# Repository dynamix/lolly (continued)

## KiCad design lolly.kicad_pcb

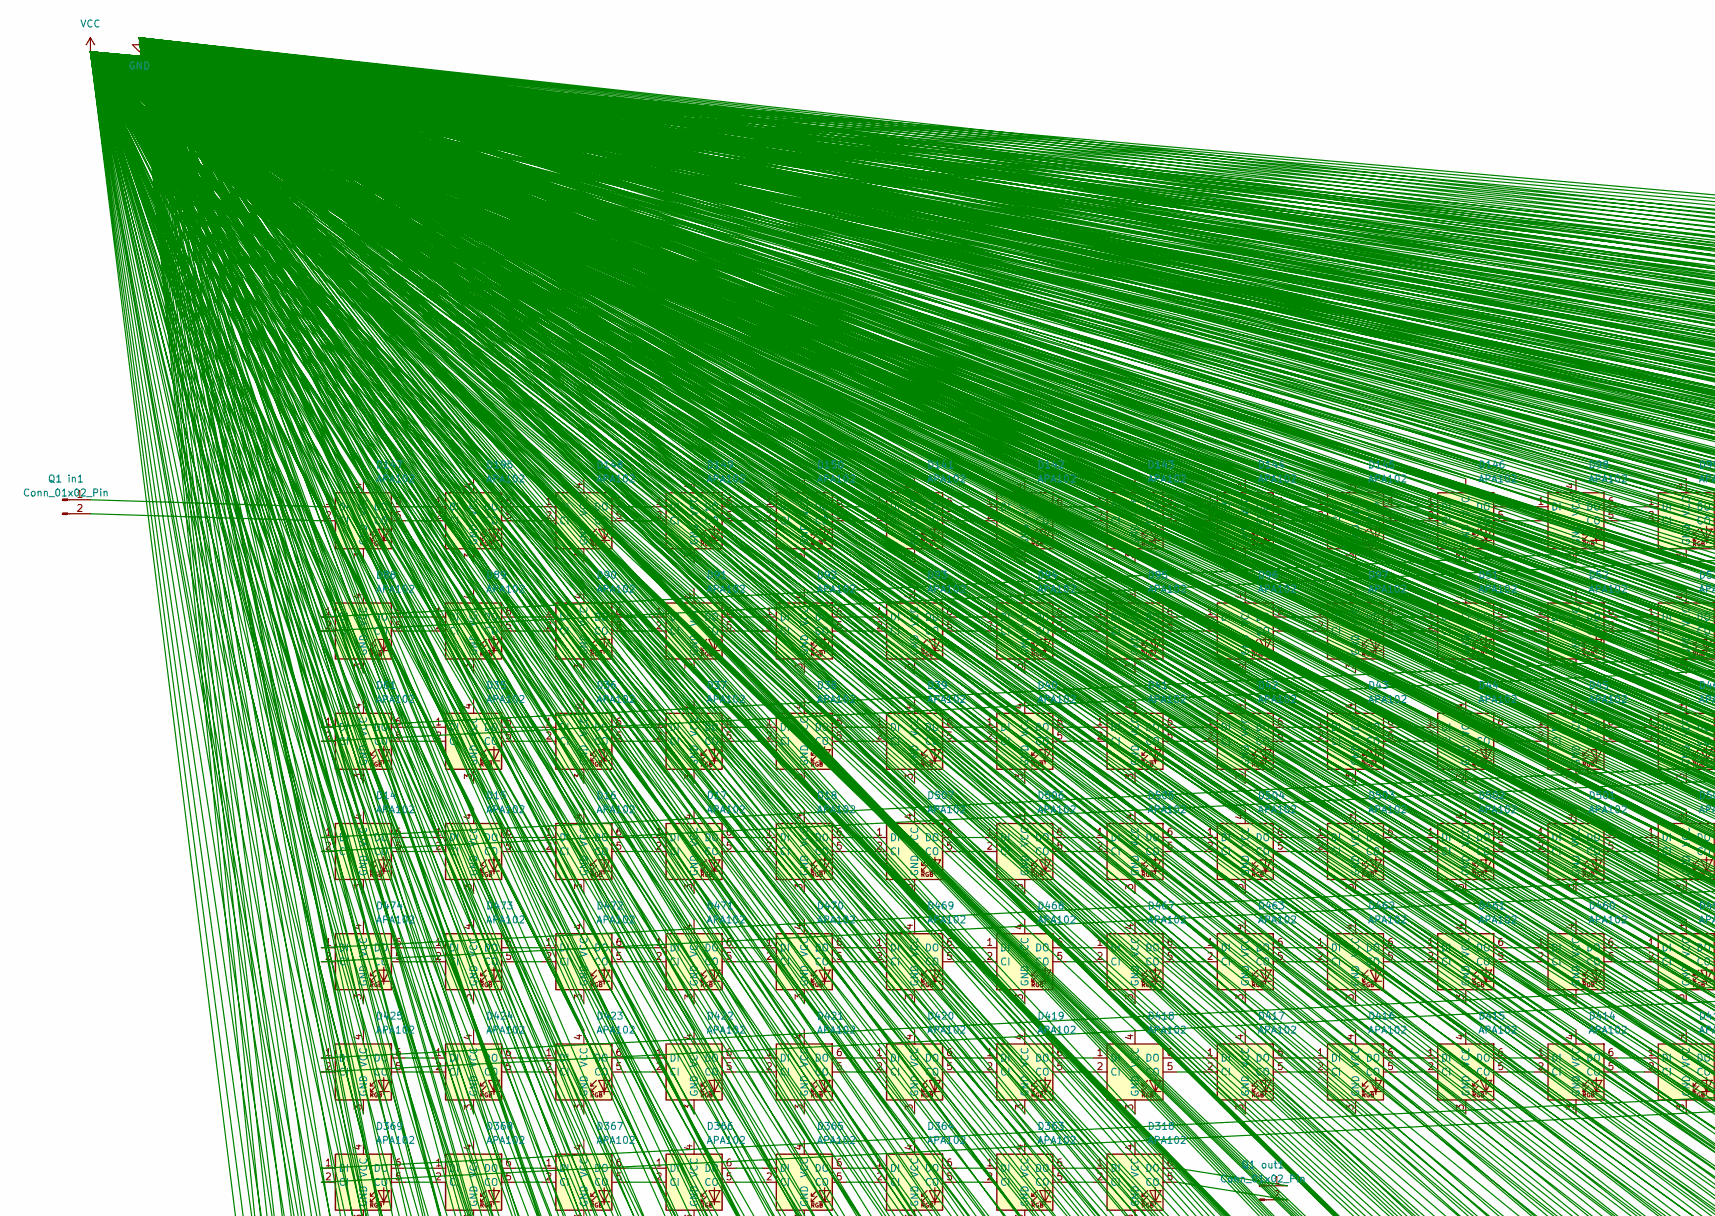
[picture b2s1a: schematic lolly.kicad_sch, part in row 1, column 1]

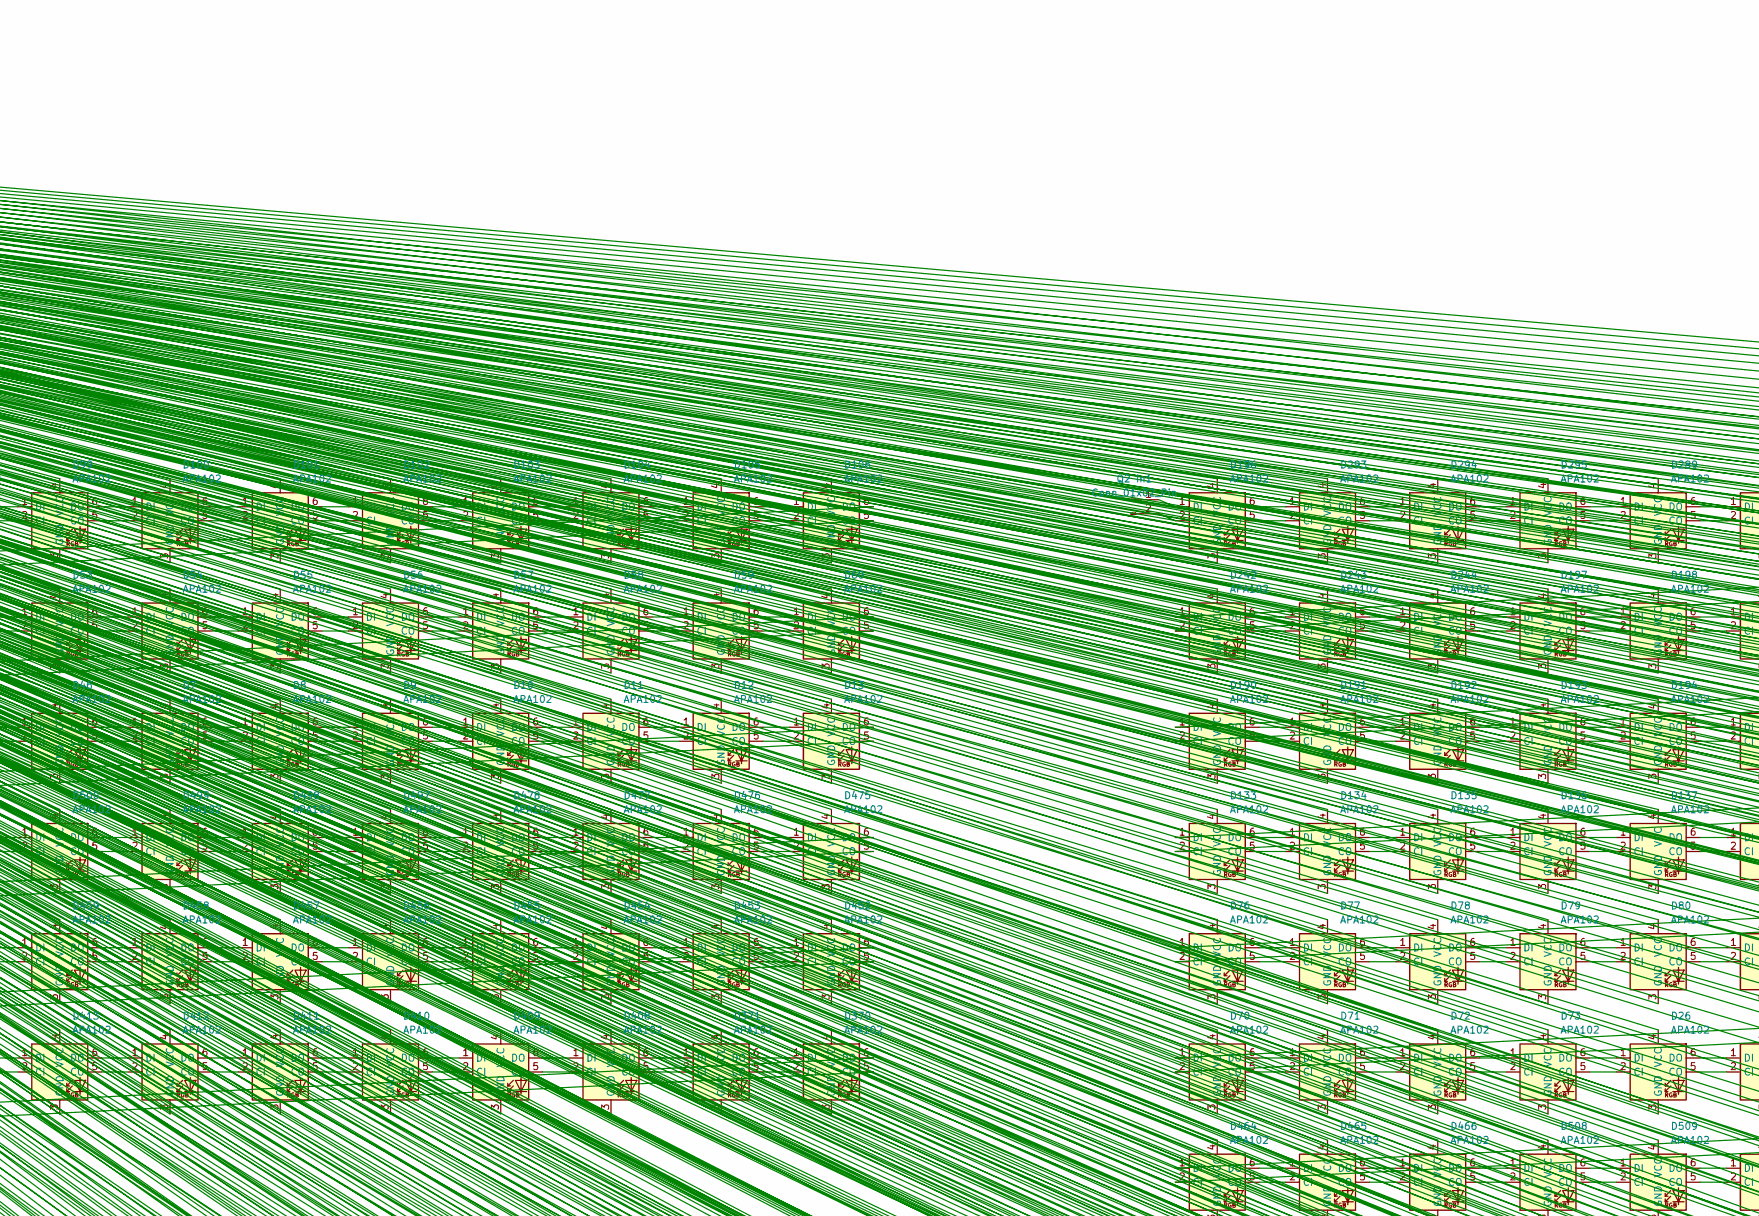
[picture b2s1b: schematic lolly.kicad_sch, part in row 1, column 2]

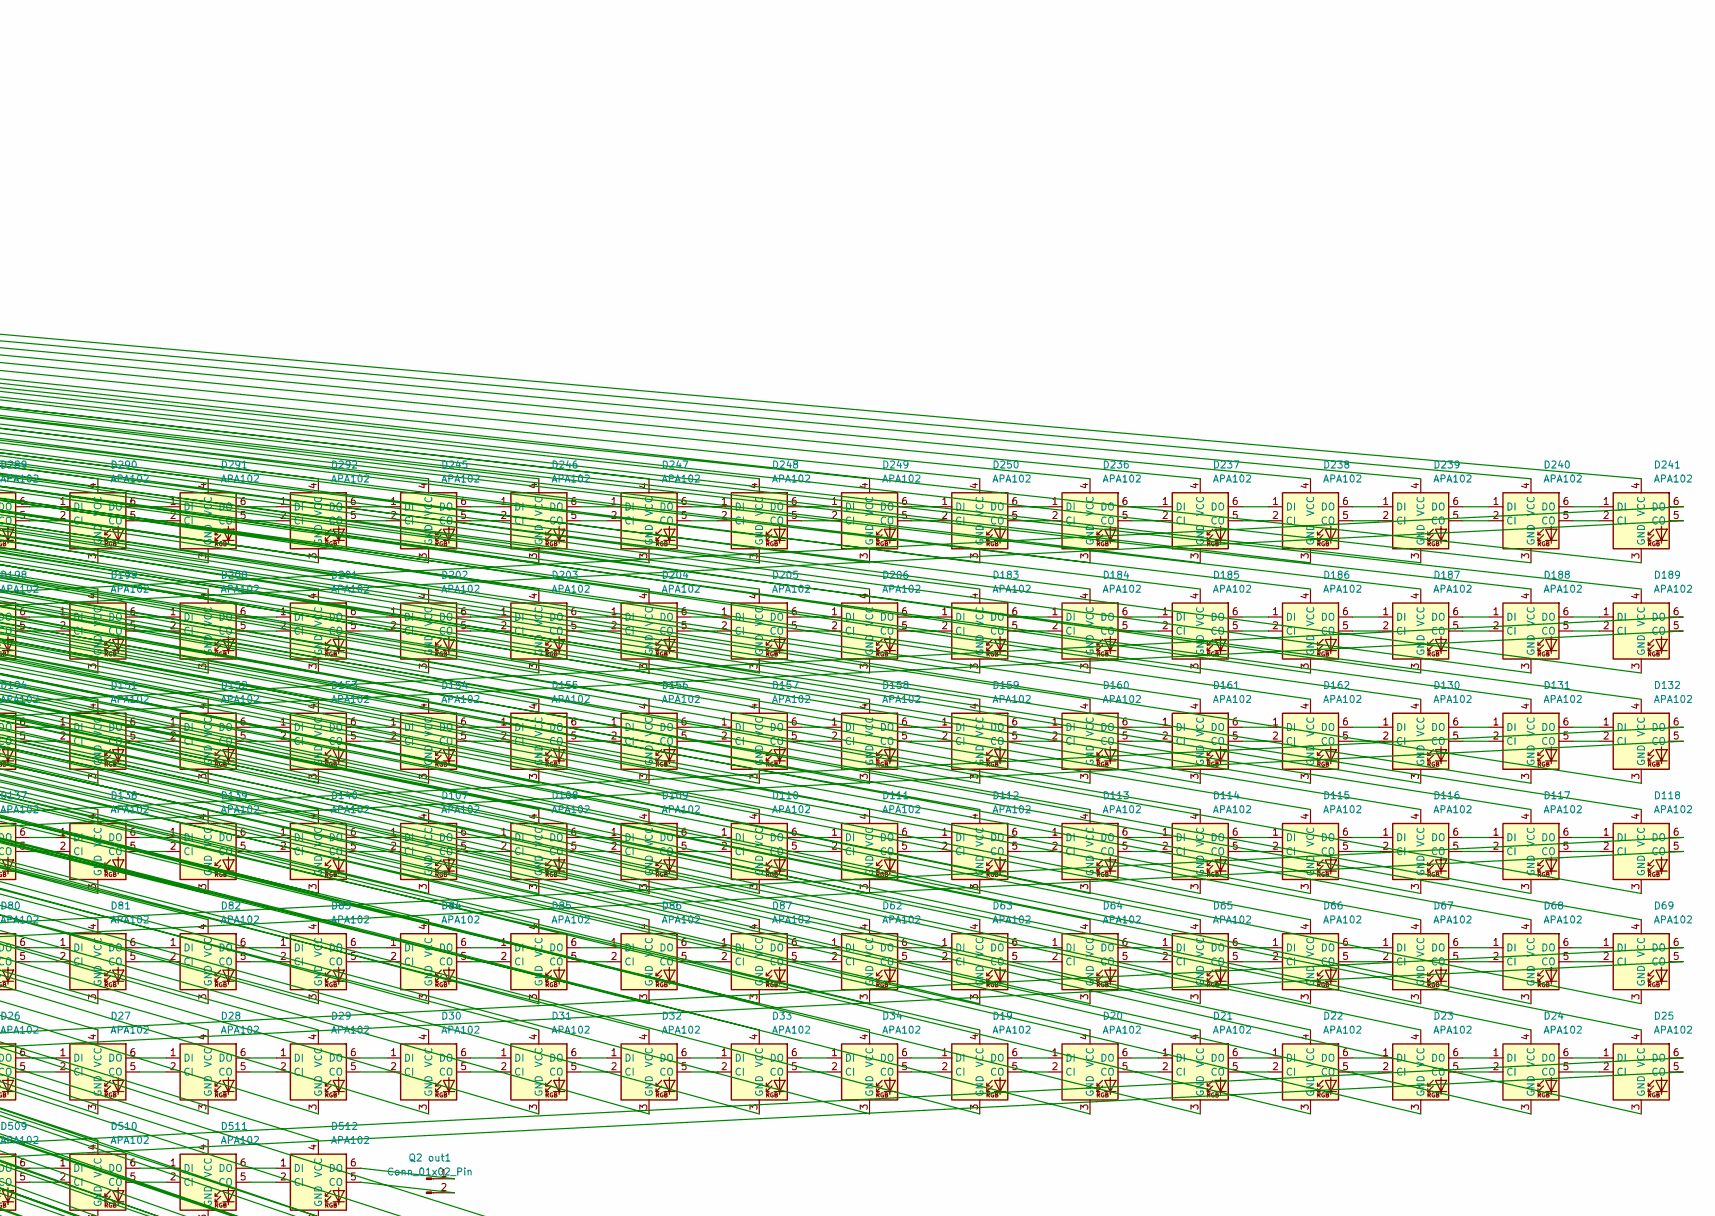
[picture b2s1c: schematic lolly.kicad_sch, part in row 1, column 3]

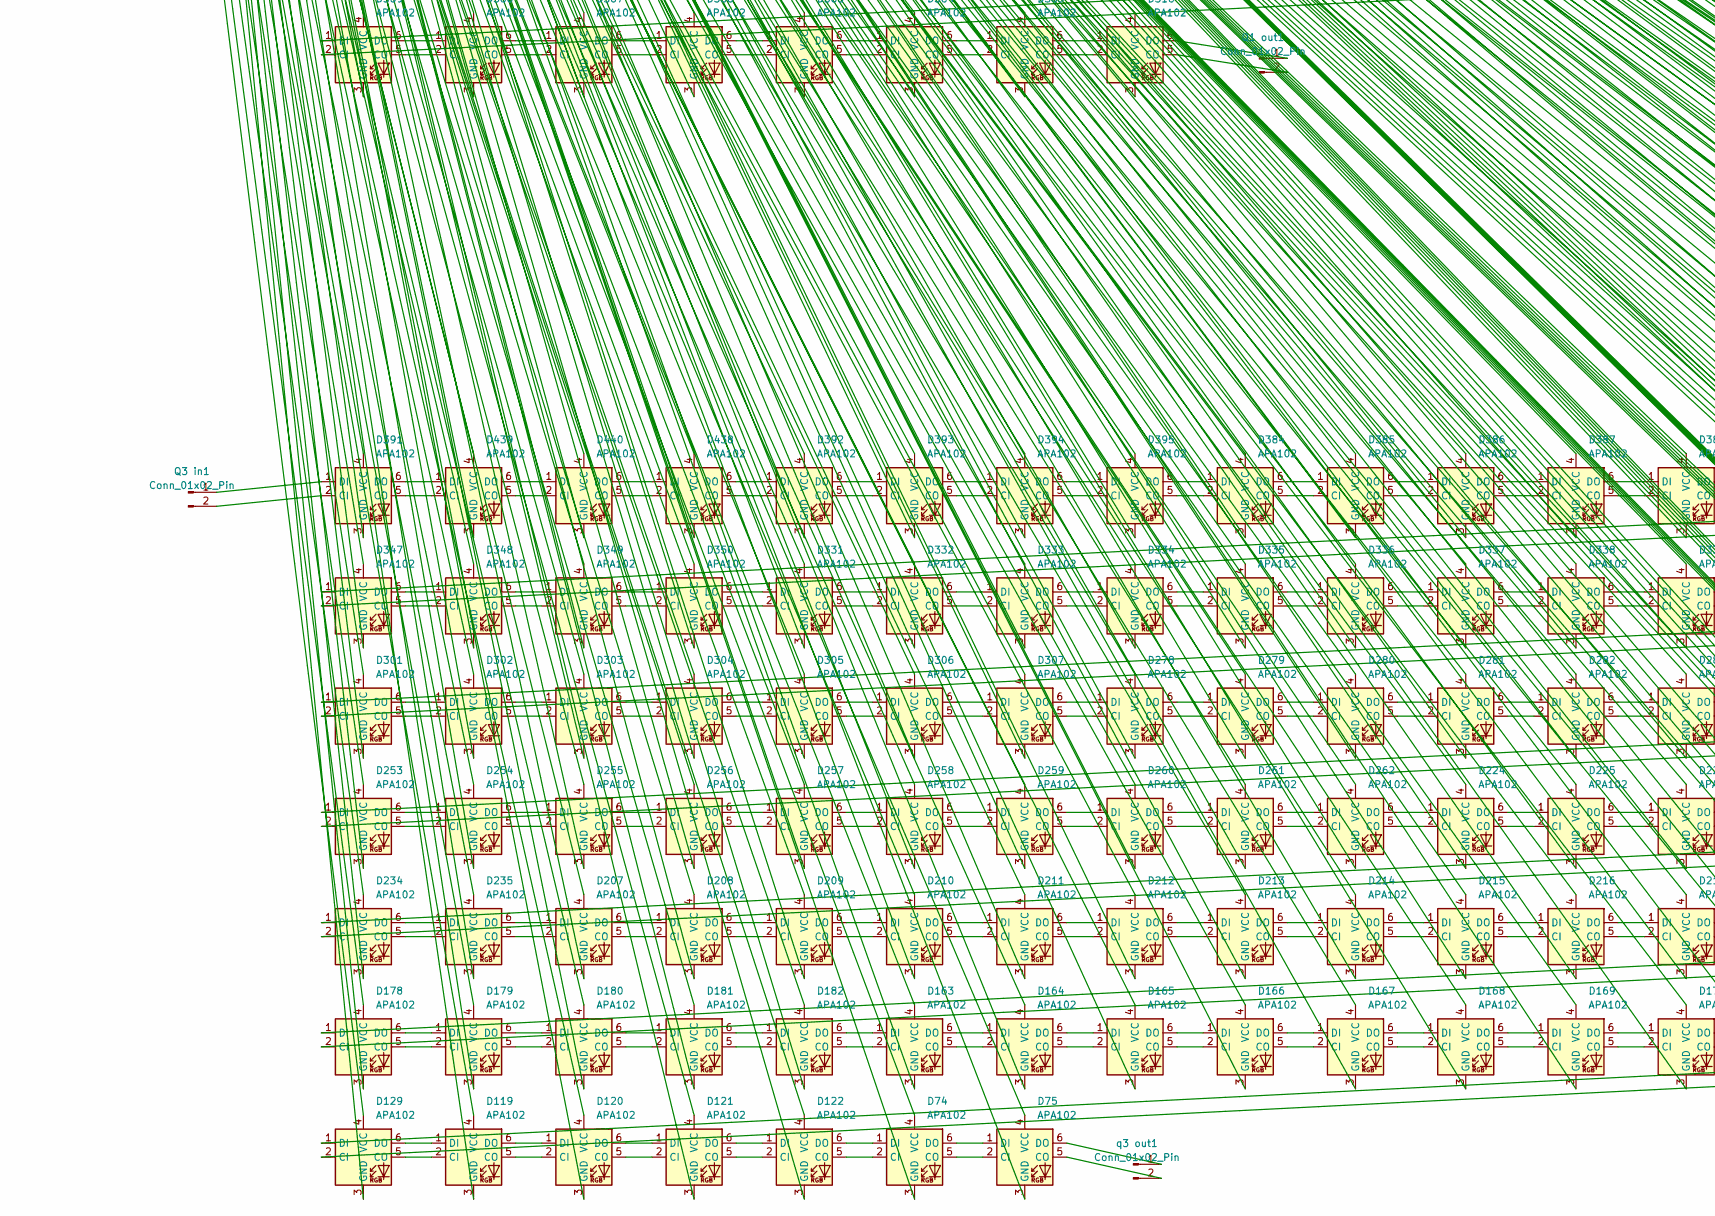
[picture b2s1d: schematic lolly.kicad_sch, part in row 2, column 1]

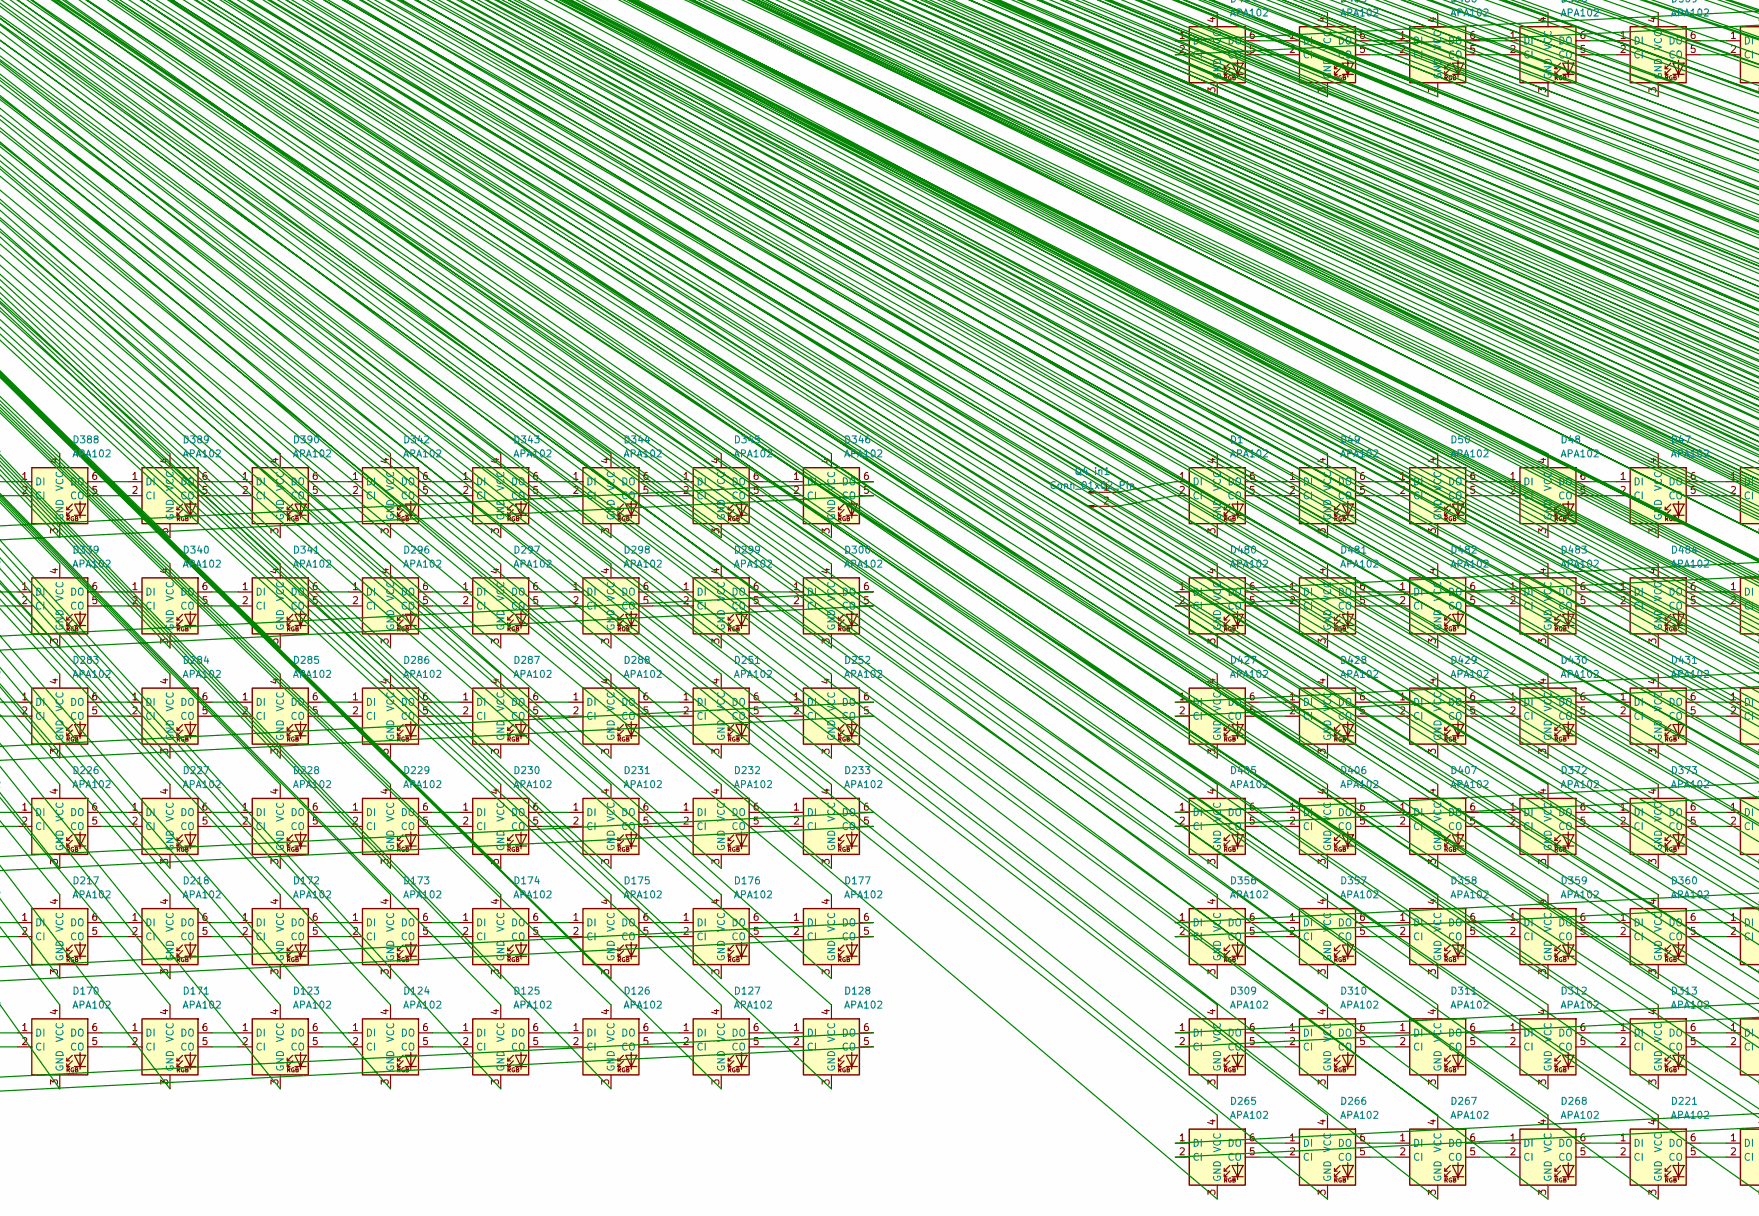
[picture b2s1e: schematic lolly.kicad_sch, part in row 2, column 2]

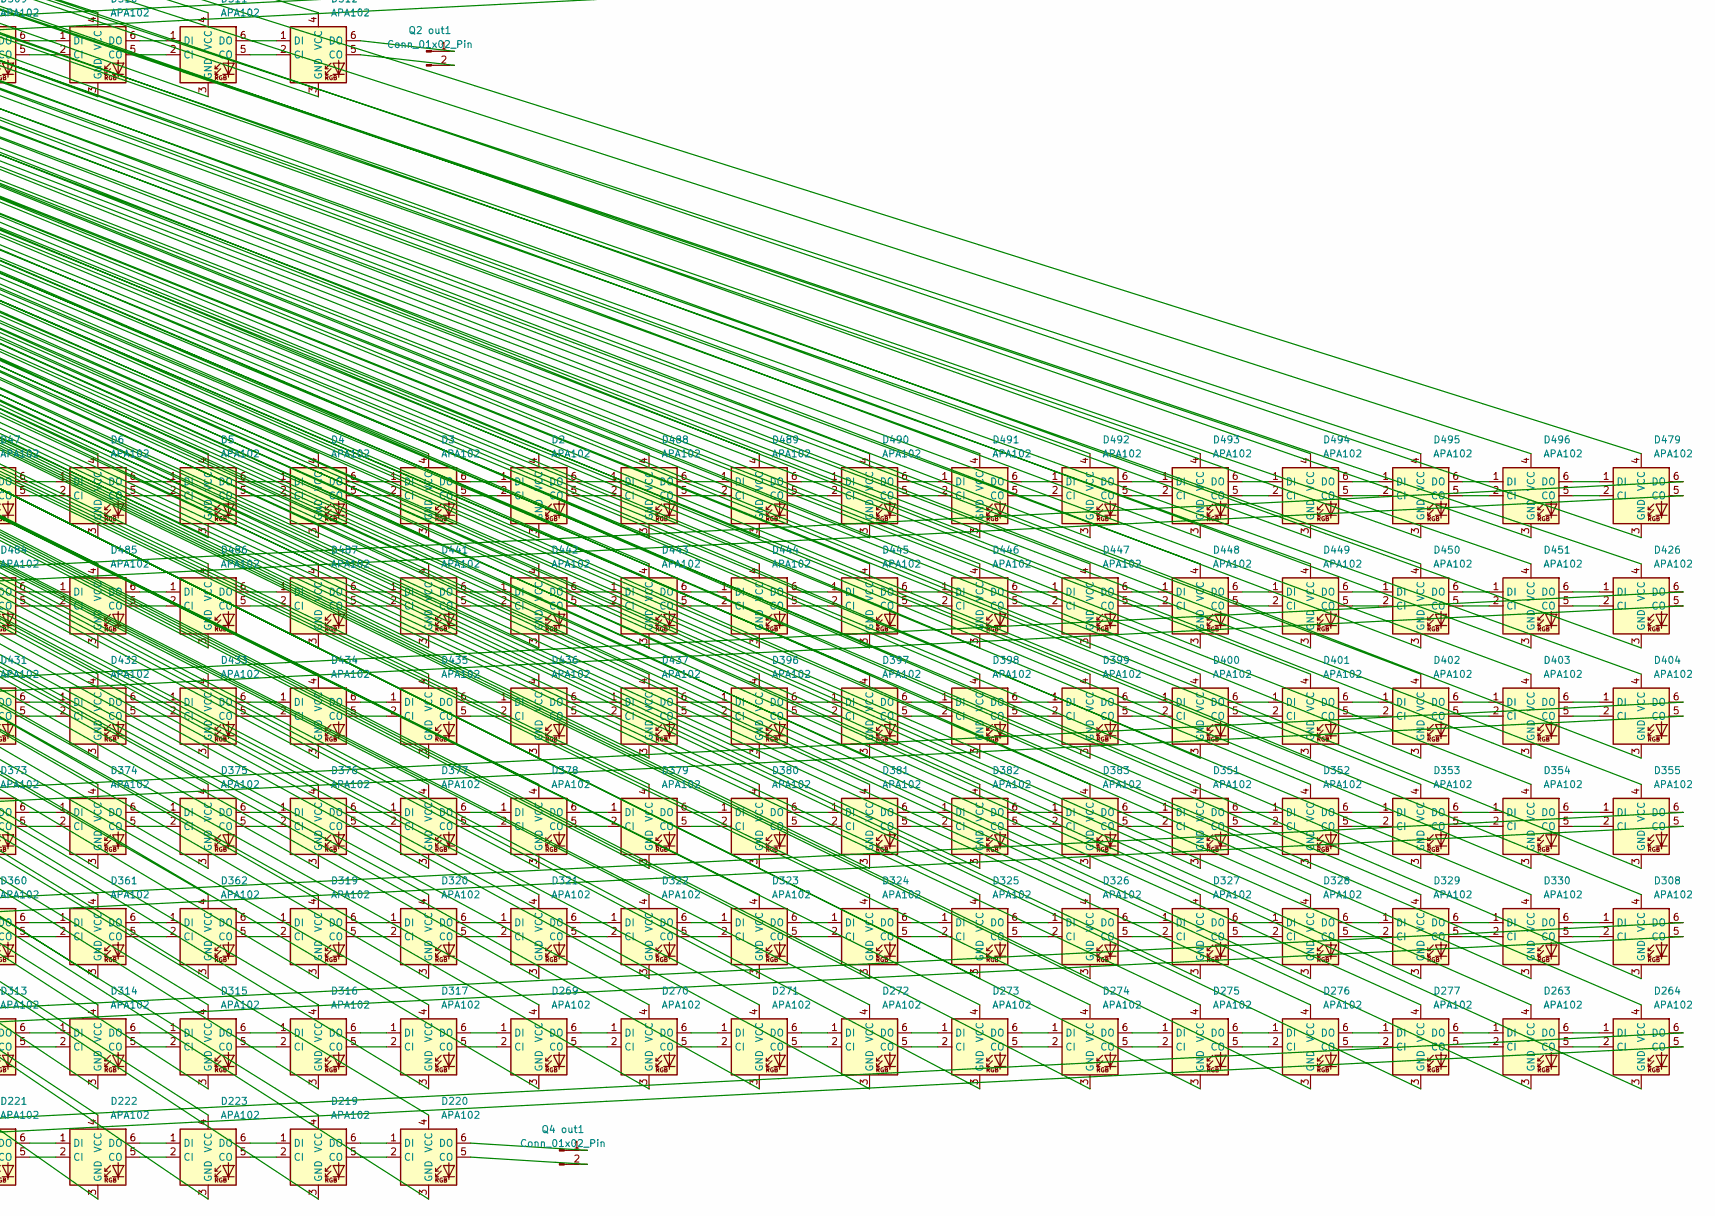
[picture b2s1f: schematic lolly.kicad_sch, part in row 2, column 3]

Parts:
D1, D2, D3, D4, D5, D6, D7, D8, D9, D10, D11, D12, D13, D14, D15, D16, D17, D18, D19, D20, D21, D22, D23, D24, D25, D26, D27, D28, D29, D30, D31, D32, D33, D34, D35, D36, D37, D38, D39, D40, D41, D42, D43, D44, D45, D46, D47, D48, D49, D50, D51, D52, D53, D54, D55, D56, D57, D58, D59, D60, D61, D62, D63, D64, D65, D66, D67, D68, D69, D70, D71, D72, D73, D74, D75, D76, D77, D78, D79, D80, D81, D82, D83, D84, D85, D86, D87, D88, D89, D90, D91, D92, D93, D94, D95, D96, D97, D98, D99, D100, D101, D102, D103, D104, D105, D106, D107, D108, D109, D110, D111, D112, D113, D114, D115, D116, D117, D118, D119, D120, D121, D122, D123, D124, D125, D126, D127, D128, D129, D130, D131, D132, D133, D134, D135, D136, D137, D138, D139, D140, D141, D142, D143, D144, D145, D146, D147, D148, D149, D150, D151, D152, D153, D154, D155, D156, D157, D158, D159, D160, D161, D162, D163, D164, D165, D166, D167, D168, D169, D170, D171, D172, D173, D174, D175, D176, D177, D178, D179, D180, D181, D182, D183, D184, D185, D186, D187, D188, D189, D190, D191, D192, D193, D194, D195, D196, D197, D198, D199, D200, D201, D202, D203, D204, D205, D206, D207, D208, D209, D210, D211, D212, D213, D214, D215, D216, D217, D218, D219, D220, D221, D222, D223, D224, D225, D226, D227, D228, D229, D230, D231, D232, D233, D234, D235, D236, D237, D238, D239, D240, D241, D242, D243, D244, D245, D246, D247, D248, D249, D250, D251, D252, D253, D254, D255, D256, D257, D258, D259, D260, D261, D262, D263, D264, D265, D266, D267, D268, D269, D270, D271, D272, D273, D274, D275, D276, D277, D278, D279, D280, D281, D282, D283, D284, D285, D286, D287, D288, D289, D290, D291, D292, D293, D294, D295, D296, D297, D298, D299, D300, D301, D302, D303, D304, D305, D306, D307, D308, D309, D310, D311, D312, D313, D314, D315, D316, D317, D318, D319, D320, D321, D322, D323, D324, D325, D326, D327, D328, D329, D330, D331, D332, D333, D334, D335, D336, D337, D338, D339, D340, D341, D342, D343, D344, D345, D346, D347, D348, D349, D350, D351, D352, D353, D354, D355, D356, D357, D358, D359, D360, D361, D362, D363, D364, D365, D366, D367, D368, D369, D370, D371, D372, D373, D374, D375, D376, D377, D378, D379, D380, D381, D382, D383, D384, D385, D386, D387, D388, D389, D390, D391, D392, D393, D394, D395, D396, D397, D398, D399, D400, D401, D402, D403, D404, D405, D406, D407, D408, D409, D410, D411, D412, D413, D414, D415, D416, D417, D418, D419, D420, D421, D422, D423, D424, D425, D426, D427, D428, D429, D430, D431, D432, D433, D434, D435, D436, D437, D438, D439, D440, D441, D442, D443, D444, D445, D446, D447, D448, D449, D450, D451, D452, D453, D454, D455, D456, D457, D458, D459, D460, D461, D462, D463, D464, D465, D466, D467, D468, D469, D470, D471, D472, D473, D474, D475, D476, D477, D478, D479, D480, D481, D482, D483, D484, D485, D486, D487, D488, D489, D490, D491, D492, D493, D494, D495, D496, D497, D498, D499, D500, D501, D502, D503, D504, D505, D506, D507, D508, D509, D510, D511, D512: APA102; LED_RGB_5050-6
Q1 in1, Q1 out1, Q2 in1, Q2 out1, Q3 in1, Q4 in1, Q4 out1: Conn_01x02_Pin; JST_PH_B2B-PH-K_1x02_P2.00mm_Vertical
q3 out1: Conn_01x02_Pin; JST_PH_B2B-PH-K_1x02_P2.00mm_Vertical

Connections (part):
GND: D1.3 (GND), D2.3 (GND), D3.3 (GND), D4.3 (GND), D5.3 (GND), D6.3 (GND), D7.3 (GND), D8.3 (GND), D9.3 (GND), D10.3 (GND), D11.3 (GND), D12.3 (GND), D13.3 (GND), D14.3 (GND), D15.3 (GND), D16.3 (GND), D17.3 (GND), D18.3 (GND), D19.3 (GND), D20.3 (GND), D21.3 (GND), D22.3 (GND), D23.3 (GND), D24.3 (GND), D25.3 (GND), D26.3 (GND), D27.3 (GND), D28.3 (GND), D29.3 (GND), D30.3 (GND), D31.3 (GND), D32.3 (GND), D33.3 (GND), D34.3 (GND), D35.3 (GND), D36.3 (GND), D37.3 (GND), D38.3 (GND), D39.3 (GND), D40.3 (GND), D41.3 (GND), D42.3 (GND), D43.3 (GND), D44.3 (GND), D45.3 (GND), D46.3 (GND), D47.3 (GND), D48.3 (GND), D49.3 (GND), D50.3 (GND), D51.3 (GND), D52.3 (GND), D53.3 (GND), D54.3 (GND), D55.3 (GND), D56.3 (GND), D57.3 (GND), D58.3 (GND), D59.3 (GND), D60.3 (GND), D61.3 (GND), D62.3 (GND), D63.3 (GND), D64.3 (GND), D65.3 (GND), D66.3 (GND), D67.3 (GND), D68.3 (GND), D69.3 (GND), D70.3 (GND), D71.3 (GND), D72.3 (GND), D73.3 (GND), D74.3 (GND), D75.3 (GND), D76.3 (GND), D77.3 (GND), D78.3 (GND), D79.3 (GND), D80.3 (GND)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; also elsewhere on the board
unnamed: D1.2 (CI), Q4 in1.2
unnamed: D1.5 (CO), D49.2 (CI)
unnamed: D1.1 (DI), Q4 in1.1
unnamed: D1.6 (DO), D49.1 (DI)
unnamed: D2.2 (CI), D3.5 (CO)
unnamed: D2.5 (CO), D488.2 (CI)
unnamed: D2.1 (DI), D3.6 (DO)
unnamed: D2.6 (DO), D488.1 (DI)
unnamed: D3.2 (CI), D4.5 (CO)
unnamed: D3.1 (DI), D4.6 (DO)
unnamed: D4.2 (CI), D5.5 (CO)
unnamed: D4.1 (DI), D5.6 (DO)
unnamed: D5.2 (CI), D6.5 (CO)
unnamed: D5.1 (DI), D6.6 (DO)
unnamed: D7.5 (CO), D8.2 (CI)
unnamed: D7.6 (DO), D8.1 (DI)
unnamed: D8.5 (CO), D9.2 (CI)
unnamed: D8.6 (DO), D9.1 (DI)
unnamed: D9.5 (CO), D10.2 (CI)
unnamed: D10.5 (CO), D11.2 (CI)
unnamed: D9.6 (DO), D10.1 (DI)
unnamed: D10.6 (DO), D11.1 (DI)
unnamed: D11.5 (CO), D12.2 (CI)
unnamed: D11.6 (DO), D12.1 (DI)
unnamed: D12.5 (CO), D13.2 (CI)
unnamed: D12.6 (DO), D13.1 (DI)
unnamed: D13.5 (CO), D14.2 (CI)
unnamed: D13.6 (DO), D14.1 (DI)
unnamed: D14.5 (CO), D15.2 (CI)
unnamed: D14.6 (DO), D15.1 (DI)
unnamed: D15.5 (CO), D16.2 (CI)
unnamed: D15.6 (DO), D16.1 (DI)
unnamed: D16.5 (CO), D17.2 (CI)
unnamed: D16.6 (DO), D17.1 (DI)
unnamed: D17.5 (CO), D18.2 (CI)
unnamed: D17.6 (DO), D18.1 (DI)
unnamed: D18.5 (CO), D507.2 (CI)
unnamed: D18.6 (DO), D507.1 (DI)
unnamed: D19.2 (CI), D34.5 (CO)
unnamed: D19.5 (CO), D20.2 (CI)
unnamed: D19.1 (DI), D34.6 (DO)
unnamed: D19.6 (DO), D20.1 (DI)
unnamed: D20.5 (CO), D21.2 (CI)
unnamed: D20.6 (DO), D21.1 (DI)
unnamed: D21.5 (CO), D22.2 (CI)
unnamed: D21.6 (DO), D22.1 (DI)
unnamed: D22.5 (CO), D23.2 (CI)
unnamed: D22.6 (DO), D23.1 (DI)
unnamed: D23.5 (CO), D24.2 (CI)
unnamed: D23.6 (DO), D24.1 (DI)
unnamed: D24.5 (CO), D25.2 (CI)
unnamed: D24.6 (DO), D25.1 (DI)
unnamed: D25.5 (CO), D464.2 (CI)
unnamed: D25.6 (DO), D464.1 (DI)
unnamed: D26.2 (CI), D73.5 (CO)
unnamed: D26.5 (CO), D27.2 (CI)
unnamed: D26.1 (DI), D73.6 (DO)
unnamed: D26.6 (DO), D27.1 (DI)
unnamed: D27.5 (CO), D28.2 (CI)
unnamed: D27.6 (DO), D28.1 (DI)
unnamed: D28.5 (CO), D29.2 (CI)
unnamed: D28.6 (DO), D29.1 (DI)
unnamed: D29.5 (CO), D30.2 (CI)
unnamed: D29.6 (DO), D30.1 (DI)
unnamed: D30.5 (CO), D31.2 (CI)
unnamed: D30.6 (DO), D31.1 (DI)
unnamed: D31.5 (CO), D32.2 (CI)
unnamed: D31.6 (DO), D32.1 (DI)
unnamed: D32.5 (CO), D33.2 (CI)
unnamed: D32.6 (DO), D33.1 (DI)
unnamed: D33.5 (CO), D34.2 (CI)
unnamed: D33.6 (DO), D34.1 (DI)
unnamed: D35.2 (CI), D61.5 (CO)
unnamed: D35.5 (CO), D36.2 (CI)
unnamed: D35.1 (DI), D61.6 (DO)
unnamed: D35.6 (DO), D36.1 (DI)
unnamed: D36.5 (CO), D37.2 (CI)
unnamed: D36.6 (DO), D37.1 (DI)
unnamed: D37.5 (CO), D38.2 (CI)
unnamed: D37.6 (DO), D38.1 (DI)
unnamed: D38.5 (CO), D39.2 (CI)
unnamed: D38.6 (DO), D39.1 (DI)
unnamed: D39.5 (CO), D40.2 (CI)
unnamed: D39.6 (DO), D40.1 (DI)
unnamed: D40.5 (CO), D41.2 (CI)
unnamed: D40.6 (DO), D41.1 (DI)
unnamed: D41.5 (CO), D42.2 (CI)
unnamed: D41.6 (DO), D42.1 (DI)
unnamed: D42.5 (CO), D43.2 (CI)
unnamed: D42.6 (DO), D43.1 (DI)
unnamed: D43.5 (CO), D44.2 (CI)
unnamed: D43.6 (DO), D44.1 (DI)
unnamed: D44.5 (CO), D45.2 (CI)
unnamed: D44.6 (DO), D45.1 (DI)
unnamed: D45.5 (CO), D46.2 (CI)
unnamed: D45.6 (DO), D46.1 (DI)
unnamed: D7.2 (CI), D46.5 (CO)
unnamed: D7.1 (DI), D46.6 (DO)
unnamed: D47.2 (CI), D48.5 (CO)
unnamed: D6.2 (CI), D47.5 (CO)
unnamed: D47.1 (DI), D48.6 (DO)
unnamed: D6.1 (DI), D47.6 (DO)
unnamed: D48.2 (CI), D50.5 (CO)
unnamed: D48.1 (DI), D50.6 (DO)
unnamed: D49.5 (CO), D50.2 (CI)
unnamed: D49.6 (DO), D50.1 (DI)
unnamed: D51.2 (CI), D97.5 (CO)
unnamed: D51.5 (CO), D52.2 (CI)
unnamed: D51.1 (DI), D97.6 (DO)
unnamed: D51.6 (DO), D52.1 (DI)
unnamed: D52.5 (CO), D53.2 (CI)
unnamed: D52.6 (DO), D53.1 (DI)
unnamed: D53.5 (CO), D54.2 (CI)
unnamed: D53.6 (DO), D54.1 (DI)
unnamed: D54.5 (CO), D55.2 (CI)
unnamed: D54.6 (DO), D55.1 (DI)
unnamed: D55.5 (CO), D56.2 (CI)
unnamed: D55.6 (DO), D56.1 (DI)
unnamed: D56.5 (CO), D57.2 (CI)
unnamed: D56.6 (DO), D57.1 (DI)
unnamed: D57.5 (CO), D58.2 (CI)
unnamed: D57.6 (DO), D58.1 (DI)
unnamed: D58.5 (CO), D59.2 (CI)
unnamed: D58.6 (DO), D59.1 (DI)
unnamed: D59.5 (CO), D60.2 (CI)
unnamed: D59.6 (DO), D60.1 (DI)
unnamed: D60.5 (CO), D61.2 (CI)
unnamed: D60.6 (DO), D61.1 (DI)
unnamed: D62.2 (CI), D87.5 (CO)
unnamed: D62.5 (CO), D63.2 (CI)
unnamed: D62.1 (DI), D87.6 (DO)
unnamed: D62.6 (DO), D63.1 (DI)
unnamed: D63.5 (CO), D64.2 (CI)
unnamed: D63.6 (DO), D64.1 (DI)
unnamed: D64.5 (CO), D65.2 (CI)
unnamed: D64.6 (DO), D65.1 (DI)
unnamed: D65.5 (CO), D66.2 (CI)
unnamed: D65.6 (DO), D66.1 (DI)
unnamed: D66.5 (CO), D67.2 (CI)
unnamed: D66.6 (DO), D67.1 (DI)
unnamed: D67.5 (CO), D68.2 (CI)
unnamed: D67.6 (DO), D68.1 (DI)
unnamed: D68.5 (CO), D69.2 (CI)
unnamed: D68.6 (DO), D69.1 (DI)
unnamed: D69.5 (CO), D70.2 (CI)
unnamed: D69.6 (DO), D70.1 (DI)
unnamed: D70.5 (CO), D71.2 (CI)
unnamed: D70.6 (DO), D71.1 (DI)
unnamed: D71.5 (CO), D72.2 (CI)
unnamed: D71.6 (DO), D72.1 (DI)
unnamed: D72.5 (CO), D73.2 (CI)
unnamed: D72.6 (DO), D73.1 (DI)
unnamed: D74.5 (CO), D75.2 (CI)
unnamed: D74.6 (DO), D75.1 (DI)
unnamed: D75.5 (CO), q3 out1.2
unnamed: D75.6 (DO), q3 out1.1
unnamed: D76.5 (CO), D77.2 (CI)
unnamed: D76.6 (DO), D77.1 (DI)
unnamed: D77.5 (CO), D78.2 (CI)
unnamed: D77.6 (DO), D78.1 (DI)
unnamed: D78.5 (CO), D79.2 (CI)
unnamed: D78.6 (DO), D79.1 (DI)
unnamed: D79.5 (CO), D80.2 (CI)
unnamed: D79.6 (DO), D80.1 (DI)
unnamed: D80.5 (CO), D81.2 (CI)
unnamed: D80.6 (DO), D81.1 (DI)
unnamed: D81.5 (CO), D82.2 (CI)
unnamed: D81.6 (DO), D82.1 (DI)
unnamed: D82.5 (CO), D83.2 (CI)
unnamed: D82.6 (DO), D83.1 (DI)
unnamed: D83.5 (CO), D84.2 (CI)
unnamed: D83.6 (DO), D84.1 (DI)
unnamed: D84.5 (CO), D85.2 (CI)
unnamed: D84.6 (DO), D85.1 (DI)
unnamed: D85.5 (CO), D86.2 (CI)
unnamed: D85.6 (DO), D86.1 (DI)
unnamed: D86.5 (CO), D87.2 (CI)
unnamed: D86.6 (DO), D87.1 (DI)
unnamed: D88.5 (CO), D89.2 (CI)
unnamed: D88.6 (DO), D89.1 (DI)
unnamed: D89.5 (CO), D90.2 (CI)
unnamed: D89.6 (DO), D90.1 (DI)
unnamed: D90.5 (CO), D91.2 (CI)
unnamed: D90.6 (DO), D91.1 (DI)
unnamed: D91.5 (CO), D92.2 (CI)
unnamed: D91.6 (DO), D92.1 (DI)
unnamed: D92.5 (CO), D93.2 (CI)
unnamed: D92.6 (DO), D93.1 (DI)
unnamed: D93.5 (CO), D94.2 (CI)
unnamed: D93.6 (DO), D94.1 (DI)
unnamed: D94.5 (CO), D95.2 (CI)
unnamed: D94.6 (DO), D95.1 (DI)
unnamed: D95.5 (CO), D96.2 (CI)
unnamed: D95.6 (DO), D96.1 (DI)
unnamed: D96.5 (CO), D97.2 (CI)
unnamed: D96.6 (DO), D97.1 (DI)
unnamed: D98.5 (CO), D99.2 (CI)
unnamed: D98.6 (DO), D99.1 (DI)
unnamed: D99.5 (CO), D100.2 (CI)
unnamed: D100.5 (CO), D101.2 (CI)
unnamed: D99.6 (DO), D100.1 (DI)
unnamed: D100.6 (DO), D101.1 (DI)
unnamed: D101.5 (CO), D102.2 (CI)
unnamed: D101.6 (DO), D102.1 (DI)
unnamed: D102.5 (CO), D103.2 (CI)
unnamed: D102.6 (DO), D103.1 (DI)
unnamed: D103.5 (CO), D104.2 (CI)
unnamed: D103.6 (DO), D104.1 (DI)
unnamed: D104.5 (CO), D105.2 (CI)
unnamed: D104.6 (DO), D105.1 (DI)
unnamed: D105.5 (CO), D106.2 (CI)
unnamed: D105.6 (DO), D106.1 (DI)
unnamed: D88.2 (CI), D106.5 (CO)
unnamed: D88.1 (DI), D106.6 (DO)
unnamed: D107.2 (CI), D140.5 (CO)
unnamed: D107.5 (CO), D108.2 (CI)
unnamed: D107.1 (DI), D140.6 (DO)
unnamed: D107.6 (DO), D108.1 (DI)
unnamed: D108.5 (CO), D109.2 (CI)
unnamed: D108.6 (DO), D109.1 (DI)
unnamed: D109.5 (CO), D110.2 (CI)
unnamed: D109.6 (DO), D110.1 (DI)
unnamed: D110.5 (CO), D111.2 (CI)
unnamed: D110.6 (DO), D111.1 (DI)
unnamed: D111.5 (CO), D112.2 (CI)
unnamed: D111.6 (DO), D112.1 (DI)
unnamed: D112.5 (CO), D113.2 (CI)
unnamed: D112.6 (DO), D113.1 (DI)
unnamed: D113.5 (CO), D114.2 (CI)
unnamed: D113.6 (DO), D114.1 (DI)
unnamed: D114.5 (CO), D115.2 (CI)
unnamed: D114.6 (DO), D115.1 (DI)
unnamed: D115.5 (CO), D116.2 (CI)
unnamed: D115.6 (DO), D116.1 (DI)
unnamed: D116.5 (CO), D117.2 (CI)
unnamed: D116.6 (DO), D117.1 (DI)
unnamed: D117.5 (CO), D118.2 (CI)
unnamed: D117.6 (DO), D118.1 (DI)
unnamed: D76.2 (CI), D118.5 (CO)
unnamed: D76.1 (DI), D118.6 (DO)
unnamed: D119.2 (CI), D129.5 (CO)
unnamed: D119.5 (CO), D120.2 (CI)
unnamed: D119.1 (DI), D129.6 (DO)
unnamed: D119.6 (DO), D120.1 (DI)
unnamed: D120.5 (CO), D121.2 (CI)
unnamed: D120.6 (DO), D121.1 (DI)
unnamed: D121.5 (CO), D122.2 (CI)
unnamed: D121.6 (DO), D122.1 (DI)
unnamed: D74.2 (CI), D122.5 (CO)
unnamed: D74.1 (DI), D122.6 (DO)
unnamed: D123.2 (CI), D171.5 (CO)
unnamed: D123.5 (CO), D124.2 (CI)
unnamed: D123.1 (DI), D171.6 (DO)
unnamed: D123.6 (DO), D124.1 (DI)
unnamed: D124.5 (CO), D125.2 (CI)
unnamed: D124.6 (DO), D125.1 (DI)
unnamed: D125.5 (CO), D126.2 (CI)
unnamed: D125.6 (DO), D126.1 (DI)
unnamed: D126.5 (CO), D127.2 (CI)
unnamed: D126.6 (DO), D127.1 (DI)
unnamed: D127.5 (CO), D128.2 (CI)
unnamed: D127.6 (DO), D128.1 (DI)
unnamed: D128.5 (CO), D129.2 (CI)
unnamed: D128.6 (DO), D129.1 (DI)
unnamed: D130.2 (CI), D162.5 (CO)
unnamed: D130.5 (CO), D131.2 (CI)
unnamed: D130.1 (DI), D162.6 (DO)
unnamed: D130.6 (DO), D131.1 (DI)
unnamed: D131.5 (CO), D132.2 (CI)
unnamed: D131.6 (DO), D132.1 (DI)
unnamed: D132.5 (CO), D133.2 (CI)
unnamed: D132.6 (DO), D133.1 (DI)
unnamed: D133.5 (CO), D134.2 (CI)
unnamed: D133.6 (DO), D134.1 (DI)
unnamed: D134.5 (CO), D135.2 (CI)
unnamed: D134.6 (DO), D135.1 (DI)
unnamed: D135.5 (CO), D136.2 (CI)
unnamed: D135.6 (DO), D136.1 (DI)
unnamed: D136.5 (CO), D137.2 (CI)
unnamed: D136.6 (DO), D137.1 (DI)
unnamed: D137.5 (CO), D138.2 (CI)
unnamed: D137.6 (DO), D138.1 (DI)
unnamed: D138.5 (CO), D139.2 (CI)
unnamed: D138.6 (DO), D139.1 (DI)
unnamed: D139.5 (CO), D140.2 (CI)
unnamed: D139.6 (DO), D140.1 (DI)
unnamed: D141.2 (CI), D150.5 (CO)
unnamed: D141.5 (CO), D142.2 (CI)
unnamed: D141.1 (DI), D150.6 (DO)
unnamed: D141.6 (DO), D142.1 (DI)
unnamed: D142.5 (CO), D143.2 (CI)
unnamed: D142.6 (DO), D143.1 (DI)
unnamed: D143.5 (CO), D144.2 (CI)
unnamed: D143.6 (DO), D144.1 (DI)
unnamed: D144.5 (CO), D145.2 (CI)
unnamed: D144.6 (DO), D145.1 (DI)
unnamed: D145.5 (CO), D146.2 (CI)
unnamed: D145.6 (DO), D146.1 (DI)
unnamed: D98.2 (CI), D146.5 (CO)
unnamed: D98.1 (DI), D146.6 (DO)
unnamed: D147.2 (CI), Q1 in1.2
unnamed: D147.5 (CO), D195.2 (CI)
unnamed: D147.1 (DI), Q1 in1.1
unnamed: D147.6 (DO), D195.1 (DI)
unnamed: D148.2 (CI), D195.5 (CO)
unnamed: D148.5 (CO), D149.2 (CI)
unnamed: D148.1 (DI), D195.6 (DO)
unnamed: D148.6 (DO), D149.1 (DI)
unnamed: D149.5 (CO), D150.2 (CI)
unnamed: D149.6 (DO), D150.1 (DI)
unnamed: D151.2 (CI), D194.5 (CO)
unnamed: D151.5 (CO), D152.2 (CI)
unnamed: D151.1 (DI), D194.6 (DO)
unnamed: D151.6 (DO), D152.1 (DI)
unnamed: D152.5 (CO), D153.2 (CI)
unnamed: D152.6 (DO), D153.1 (DI)
unnamed: D153.5 (CO), D154.2 (CI)
unnamed: D153.6 (DO), D154.1 (DI)
unnamed: D154.5 (CO), D155.2 (CI)
unnamed: D154.6 (DO), D155.1 (DI)
unnamed: D155.5 (CO), D156.2 (CI)
unnamed: D155.6 (DO), D156.1 (DI)
unnamed: D156.5 (CO), D157.2 (CI)
unnamed: D156.6 (DO), D157.1 (DI)
unnamed: D157.5 (CO), D158.2 (CI)
unnamed: D157.6 (DO), D158.1 (DI)
unnamed: D158.5 (CO), D159.2 (CI)
unnamed: D158.6 (DO), D159.1 (DI)
unnamed: D159.5 (CO), D160.2 (CI)
unnamed: D159.6 (DO), D160.1 (DI)
unnamed: D160.5 (CO), D161.2 (CI)
unnamed: D160.6 (DO), D161.1 (DI)
unnamed: D161.5 (CO), D162.2 (CI)
unnamed: D161.6 (DO), D162.1 (DI)
unnamed: D163.2 (CI), D182.5 (CO)
unnamed: D163.5 (CO), D164.2 (CI)
unnamed: D163.1 (DI), D182.6 (DO)
unnamed: D163.6 (DO), D164.1 (DI)
unnamed: D164.5 (CO), D165.2 (CI)
unnamed: D164.6 (DO), D165.1 (DI)
unnamed: D165.5 (CO), D166.2 (CI)
unnamed: D165.6 (DO), D166.1 (DI)
unnamed: D166.5 (CO), D167.2 (CI)
unnamed: D166.6 (DO), D167.1 (DI)
unnamed: D167.5 (CO), D168.2 (CI)
unnamed: D167.6 (DO), D168.1 (DI)
unnamed: D168.5 (CO), D169.2 (CI)
unnamed: D168.6 (DO), D169.1 (DI)
unnamed: D169.5 (CO), D170.2 (CI)
unnamed: D169.6 (DO), D170.1 (DI)
unnamed: D170.5 (CO), D171.2 (CI)
unnamed: D170.6 (DO), D171.1 (DI)
unnamed: D172.2 (CI), D218.5 (CO)
unnamed: D172.5 (CO), D173.2 (CI)
unnamed: D172.1 (DI), D218.6 (DO)
unnamed: D172.6 (DO), D173.1 (DI)
unnamed: D173.5 (CO), D174.2 (CI)
unnamed: D173.6 (DO), D174.1 (DI)
unnamed: D174.5 (CO), D175.2 (CI)
unnamed: D174.6 (DO), D175.1 (DI)
unnamed: D175.5 (CO), D176.2 (CI)
unnamed: D175.6 (DO), D176.1 (DI)
unnamed: D176.5 (CO), D177.2 (CI)
unnamed: D176.6 (DO), D177.1 (DI)
unnamed: D177.5 (CO), D178.2 (CI)
unnamed: D177.6 (DO), D178.1 (DI)
unnamed: D178.5 (CO), D179.2 (CI)
unnamed: D178.6 (DO), D179.1 (DI)
unnamed: D179.5 (CO), D180.2 (CI)
unnamed: D179.6 (DO), D180.1 (DI)
unnamed: D180.5 (CO), D181.2 (CI)
unnamed: D180.6 (DO), D181.1 (DI)
unnamed: D181.5 (CO), D182.2 (CI)
unnamed: D181.6 (DO), D182.1 (DI)
unnamed: D183.2 (CI), D206.5 (CO)
unnamed: D183.5 (CO), D184.2 (CI)
unnamed: D183.1 (DI), D206.6 (DO)
unnamed: D183.6 (DO), D184.1 (DI)
unnamed: D184.5 (CO), D185.2 (CI)
unnamed: D184.6 (DO), D185.1 (DI)
unnamed: D185.5 (CO), D186.2 (CI)
unnamed: D185.6 (DO), D186.1 (DI)
unnamed: D186.5 (CO), D187.2 (CI)
unnamed: D186.6 (DO), D187.1 (DI)
unnamed: D187.5 (CO), D188.2 (CI)
unnamed: D187.6 (DO), D188.1 (DI)
unnamed: D188.5 (CO), D189.2 (CI)
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
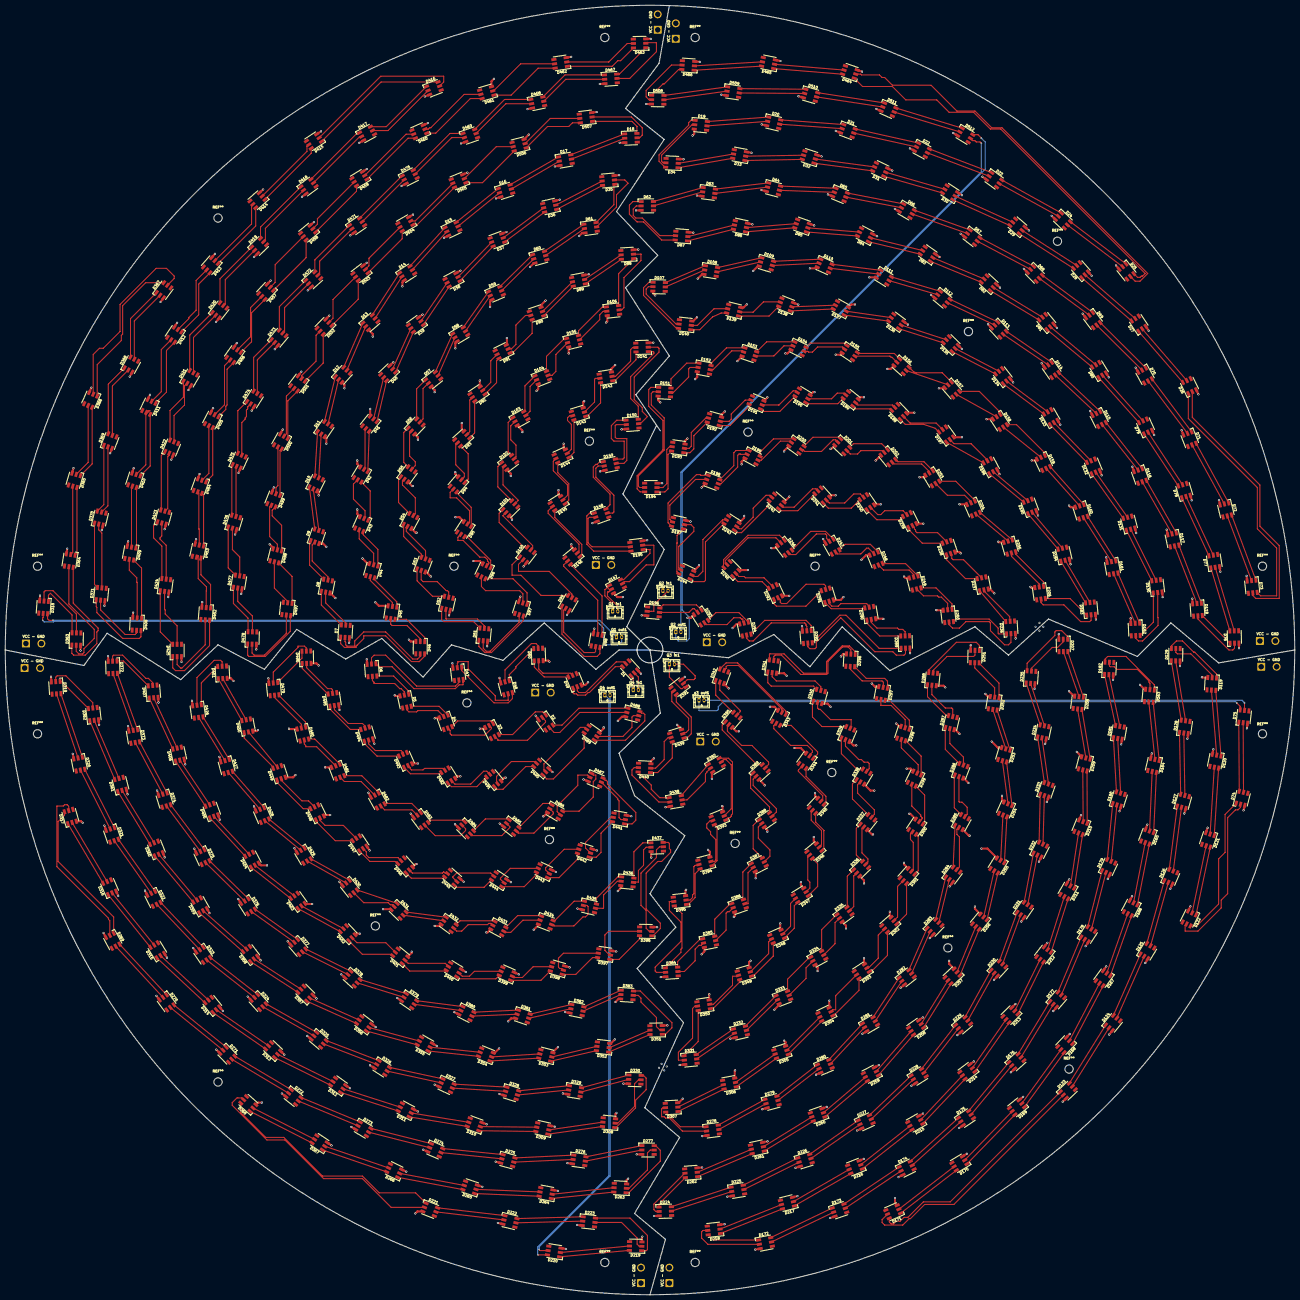
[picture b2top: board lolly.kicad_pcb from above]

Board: 2 copper layers, 500.0 x 500.0 mm, 532 parts (0 on the bottom side), 1034 nets.

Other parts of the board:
VCC - GND: SolderWire-1.5sqmm_1x02_P6mm_D1.7mm_OD3mm
VCC - GND#2, VCC - GND#3, VCC - GND#4, VCC - GND#5, VCC - GND#6, VCC - GND#7, VCC - GND#8, VCC - GND#9, VCC - GND#10, VCC - GND#11, VCC - GND#12: SolderWire-1.5sqmm_1x02_P6mm_D1.7mm_OD3mm

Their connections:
GND: VCC - GND.2, VCC - GND#2.2, VCC - GND#3.2, VCC - GND#4.2, VCC - GND#5.2, VCC - GND#6.2, VCC - GND#7.2, VCC - GND#8.2, VCC - GND#9.2, VCC - GND#10.2, VCC - GND#11.2, VCC - GND#12.2; also elsewhere on the board
VCC: VCC - GND.1, VCC - GND#2.1, VCC - GND#3.1, VCC - GND#4.1, VCC - GND#5.1, VCC - GND#6.1, VCC - GND#7.1, VCC - GND#8.1, VCC - GND#9.1, VCC - GND#10.1, VCC - GND#11.1, VCC - GND#12.1; also elsewhere on the board
